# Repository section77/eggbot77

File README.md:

# eggbot77

Section77-Variante des EggBots mit ESP32 S2 mini

Willkommen! :)

Bitte prüfe zuallererst, ob Du alle Komponenten hast, die Du zum Bau Deines EggBot77 brauchst!
* [Materialliste Mechanik](./mechanics/BOM.md)
* [Materialliste Elektronik](./electronics/BOM.md)

Alles da? Super! Dann kann's ja losgehen:
* [Aufbauanleitung Mechanik](./mechanics/assembly/README.md)
* [Aufbauanleitung Elektronik](./electronics/assembly/README.md)
* [Installationsanleitung Firmware](./firmware/README.md)
* [Installationsanleitung Inkscape Plugin](./inkscape_1.x_extension/README.md)

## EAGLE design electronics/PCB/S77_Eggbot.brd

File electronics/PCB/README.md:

Design rule file jlcpcb-2layers.dru from https://github.com/oxullo/jlcpcb-eagle

CAM File for Eagle 7.7 from
https://raw.githubusercontent.com/JLCPCBofficial/jlcpcb-eagle/master/cam/jlcpcb_2_layer_v72.cam

linked from https://jlcpcb.com/help/article/9-How-to-Generate-Gerber-and-Drill-Files-in-Autodesk-Eagle

Notes when ordering at jlcpcb. From above help page:

  "Just to be safe, you can write a special instruction in the remark area in our
  ordering system when you place the order, write like:
  "Please note: there are 3 plated slotted holes in this design".
  Our CAM engineer will sort them out from the "context"
  (like the annular ring and solder mask opening) when processing the files."

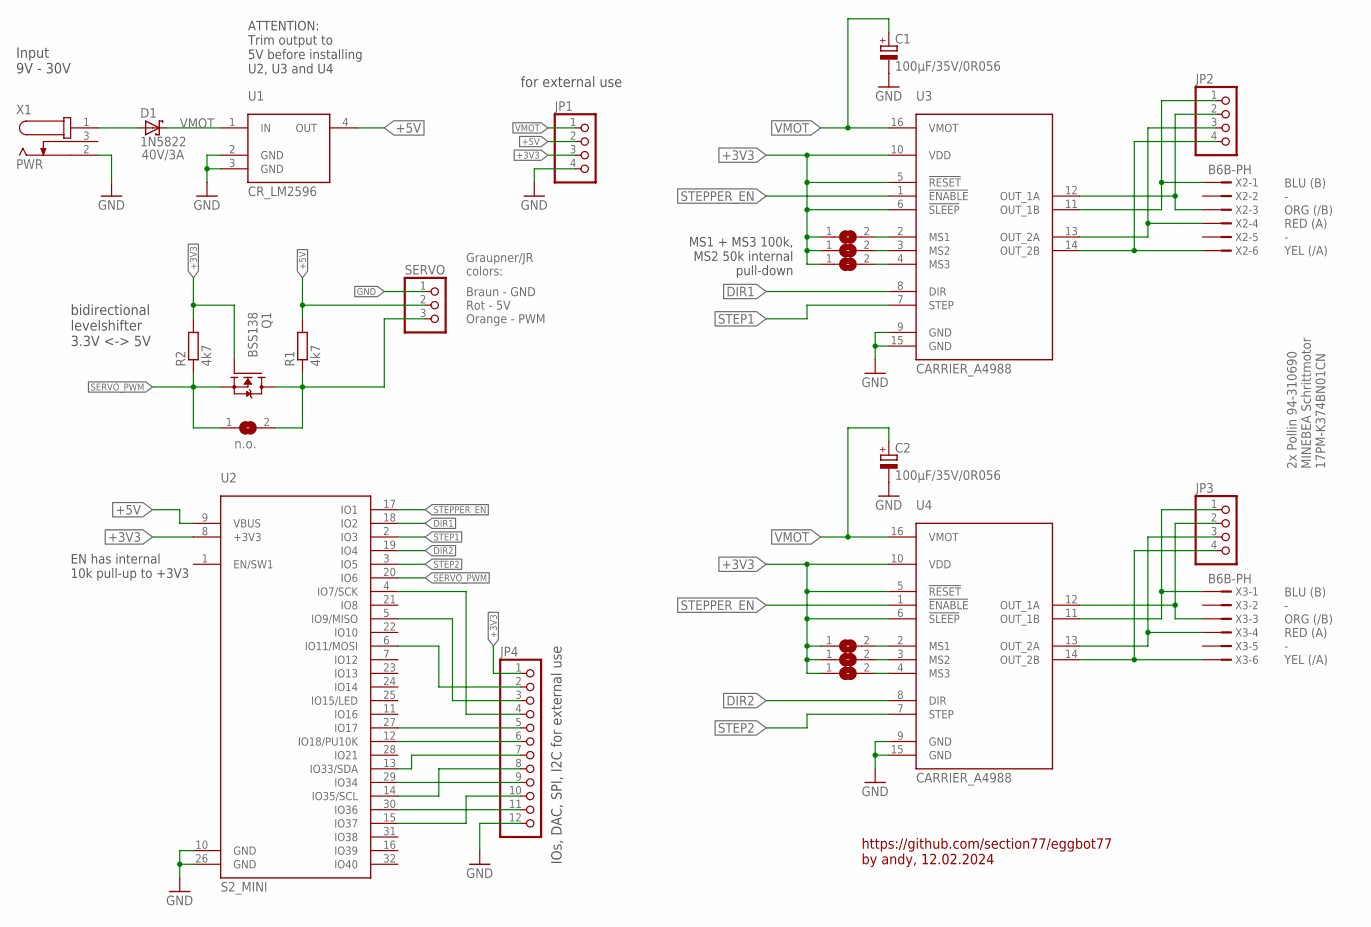
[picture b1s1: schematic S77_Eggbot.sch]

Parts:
C1, C2: 100µF/35V/0R056; E3,5-8; MPN EEUFR1V101
D1: 1N5822; DO201T15
JP1, JP2, JP3: PINHD-1X4; 1X04
JP4: PINHD-1X12; 1X12
Q1: BSS138; SOT23
R1, R2: 4k7; R1206
SERVO: PINHD-1X3; 1X03
SJ1, SJ2, SJ3, SJ4, SJ5, SJ6: SJ
SJ7: n.o.; SJ
U1: CR_LM2596
U2: S2_MINI
U3, U4: CARRIER_A4988
X1: PWR; POLLIN_JACK_A
X2, X3: B6B-PH

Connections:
+3V3: JP1.3, JP4.1, Q1.1 (G), R2.2, SJ1.1, SJ2.1, SJ3.1, SJ4.1, SJ5.1, SJ6.1, U2.8 (+3V3), U3.5 (!RESET), U3.6 (!SLEEP), U3.10 (VDD), U4.5 (!RESET), U4.6 (!SLEEP), U4.10 (VDD)
+5V: JP1.2, R1.2, SERVO.2, U1.4 (OUT), U2.9 (VBUS)
DIR1: U2.18 (IO2), U3.8 (DIR)
DIR2: U2.19 (IO4), U4.8 (DIR)
GND: C1.-, C2.-, JP1.4, JP4.12, SERVO.1, U1.2 (GND), U1.3 (GND), U2.10 (GND), U2.26 (GND), U3.9 (GND), U3.15 (GND), U4.9 (GND), U4.15 (GND), X1.2
unnamed: Q1.3 (D), R1.1, SERVO.3, SJ7.2
unnamed: JP2.1, U3.11 (OUT_1B), X2.1
unnamed: D1.A, X1.1
unnamed: JP2.2, U3.12 (OUT_1A), X2.3
unnamed: JP2.3, U3.13 (OUT_2A), X2.4
unnamed: JP2.4, U3.14 (OUT_2B), X2.6
unnamed: JP3.1, U4.11 (OUT_1B), X3.1
unnamed: JP3.2, U4.12 (OUT_1A), X3.3
unnamed: JP3.3, U4.13 (OUT_2A), X3.4
unnamed: JP3.4, U4.14 (OUT_2B), X3.6
unnamed: SJ1.2, U3.2 (MS1)
unnamed: SJ2.2, U3.3 (MS2)
unnamed: SJ3.2, U3.4 (MS3)
unnamed: SJ4.2, U4.2 (MS1)
unnamed: SJ5.2, U4.3 (MS2)
unnamed: SJ6.2, U4.4 (MS3)
unnamed: JP4.4, U2.4 (IO7/SCK)
unnamed: JP4.3, U2.5 (IO9/MISO)
unnamed: JP4.2, U2.6 (IO11/MOSI)
unnamed: JP4.5, U2.27 (IO17)
unnamed: JP4.6, U2.12 (IO18/PU10K)
unnamed: JP4.7, U2.13 (IO33/SDA)
unnamed: JP4.9, U2.29 (IO34)
unnamed: JP4.8, U2.14 (IO35/SCL)
unnamed: JP4.11, U2.30 (IO36)
unnamed: JP4.10, U2.15 (IO37)
SERVO_PWM: Q1.2 (S), R2.1, SJ7.1, U2.20 (IO6)
STEP1: U2.2 (IO3), U3.7 (STEP)
STEP2: U2.3 (IO5), U4.7 (STEP)
STEPPER_EN: U2.17 (IO1), U3.1 (!ENABLE), U4.1 (!ENABLE)
VMOT: C1.+, C2.+, D1.C, JP1.1, U1.1 (IN), U3.16 (VMOT), U4.16 (VMOT)

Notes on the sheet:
ATTENTION: Trim output to 5V before installing U2, U3 and U4
Input 9V - 30V
40V/3A
2x Pollin 94-310690 MINEBEA Schrittmotor 17PM-K374BN01CN
BLU (B) - ORG (/B) RED (A) - YEL (/A)
Braun - GND Rot - 5V Orange - PWM
MS1 + MS3 100k, MS2 50k internal pull-down
for external use
IOs, DAC, SPI, I2C for external use
EN has internal 10k pull-up to +3V3
https://github.com/section77/eggbot77 by andy, 12.02.2024
Graupner/JR colors:
bidirectional levelshifter 3.3V <-> 5V

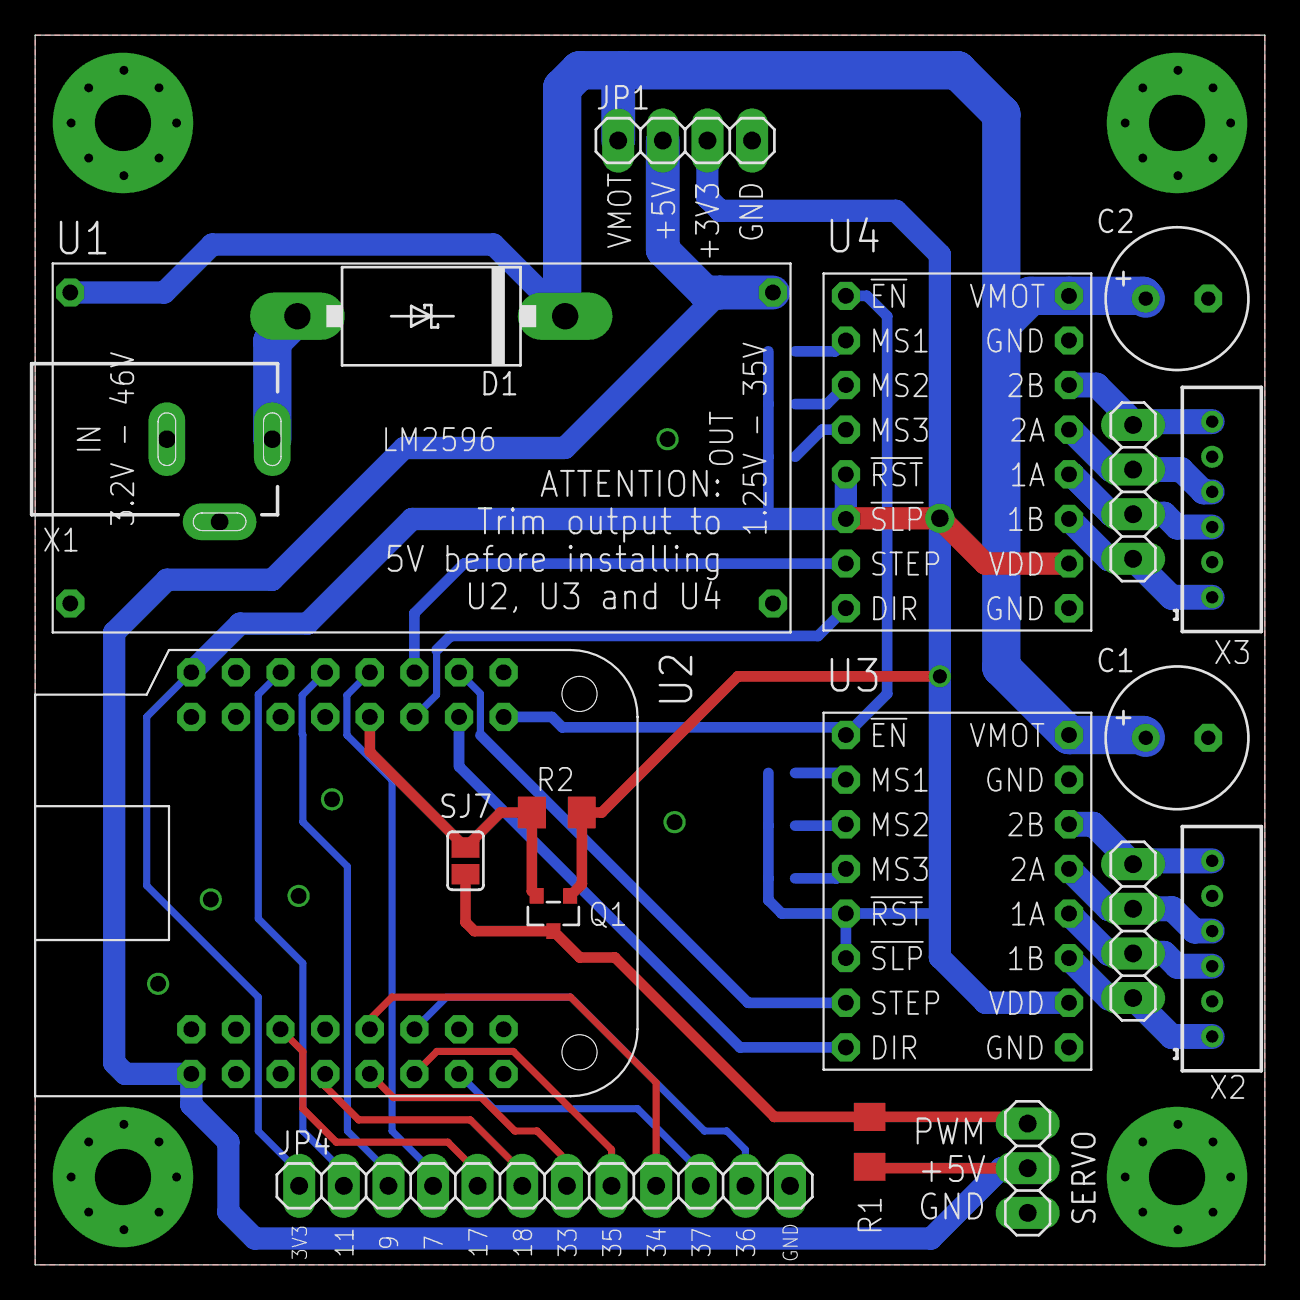
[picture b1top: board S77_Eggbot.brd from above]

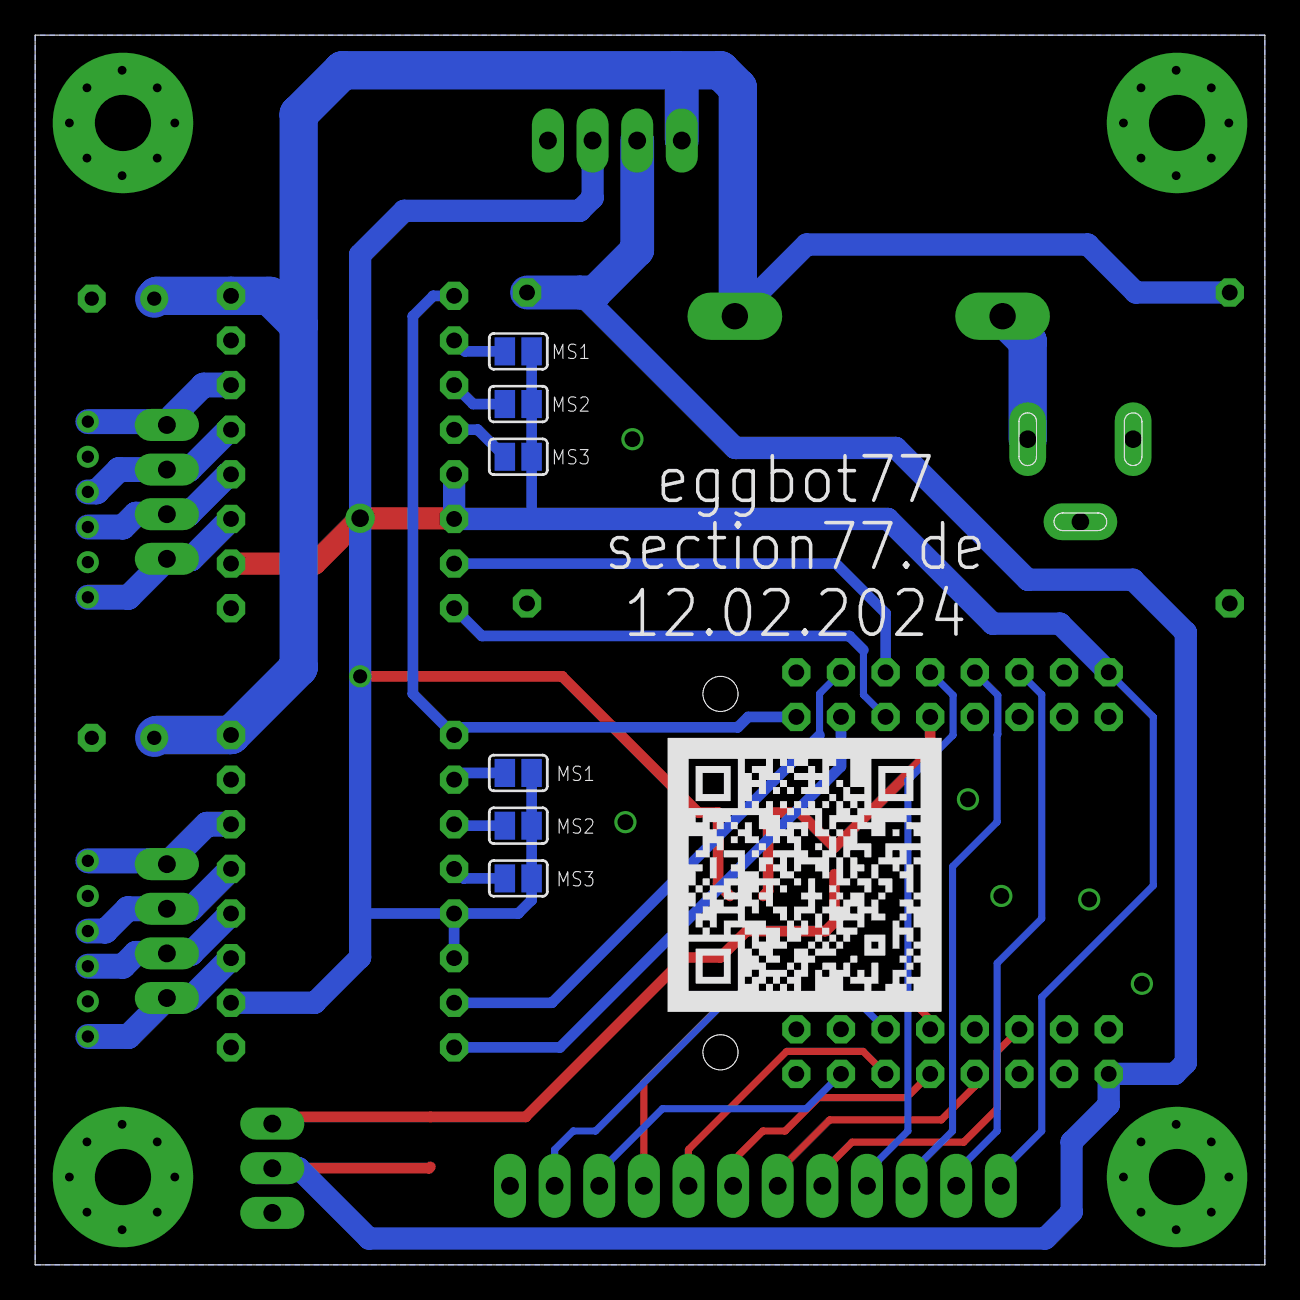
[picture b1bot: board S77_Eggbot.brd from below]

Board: 2 copper layers, 70.0 x 70.0 mm, 25 parts (6 on the bottom side), 36 nets.

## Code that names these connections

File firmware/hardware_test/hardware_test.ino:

/*
 * Simple hardware test for the EggBot77 version 25.01.2024
 * Servo sweeps between 850µs and 2150 and both steppers
 * run in velocity mode with step frequency between 440Hz and 7040 Hz.
 *
 * Attention: The stepper motors make several fast revolutions.
 * The program should therefore only be executed as long as the servo
 * and stepper motors have not yet been installed.
 */

#include <driver/ledc.h>

#define STEPPER_EN 1  // for both steppers
#define DIR1 2
#define STEP1 3
#define DIR2 4
#define STEP2 5
#define LED_BUILTIN 15  // the blue onboard LED

#define SERVO_PWM 6

// ESP32 LED Controller (we use them here for generating servo PWM and stepper frequencies)
#define SERVO_LEDC_CH 1
#define STEP1_LEDC_CH 2
#define STEP2_LEDC_CH 3

#define FREQ_HIGH 7040
#define FREQ_LOW 220

hw_timer_t *Timer0_Cfg = NULL;

void set_freq(uint8_t ch, int16_t freq) {
  ledcSetup(ch, freq, 10);  // 14bit
  ledcWrite(ch, (1 << 9));  // 50% duty cycle
}

// 200Hz/5ms task
void IRAM_ATTR Timer0_ISR() {
  static uint16_t cnt = 0;

  // toggle blue onboard LED every 500ms
  if (cnt % 100 == 0)
    digitalWrite(LED_BUILTIN, !digitalRead(LED_BUILTIN));

  // sweep servo
  {
    const int16_t min_width = 850;   // [µs]
    const int16_t max_width = 2150;  // [µs]
    static int8_t pwm_inc = 1;       // ramp slope, µs width per 10ms

    static int16_t pwm_width = min_width;
    pwm_width += pwm_inc;
    if (pwm_width > max_width) {
      pwm_width = max_width;
      pwm_inc *= -1;
    } else if (pwm_width < min_width) {
      pwm_width = min_width;
      pwm_inc *= -1;
    }
    int16_t pwm_val = pwm_width * 4096 / 20000;
    ledcWrite(SERVO_LEDC_CH, pwm_val);
  }

  // both servos in velocity mode
  // change frequency every second
  if (cnt % 200 == 0) {
    static int16_t freq = FREQ_LOW;
    static int8_t freq_dir = 1;  // 0 = down, 1 = up

    if (freq_dir == 1) {
      freq = freq * 2;
      if (freq >= FREQ_HIGH) {
        freq_dir = 0;
      }
    } else if (freq_dir == 0) {
      freq = freq / 2;
      if (freq <= FREQ_LOW) {
        freq = FREQ_LOW;
        freq_dir = 1;
        digitalWrite(DIR1, !digitalRead(DIR1));
        digitalWrite(DIR2, !digitalRead(DIR2));
      }
    }
    Serial.printf("Setting stepper frequency to %i Hz...\n", freq);
    set_freq(STEP1_LEDC_CH, freq);
    set_freq(STEP2_LEDC_CH, freq);
  }
  cnt++;
}

void setup() {
  Serial.begin(9600);
  Serial.setDebugOutput(true);

  // delay 2000ms so the Serial Monitor can reconnect to USB CDC after flashing
  delay(2000);
  Serial.println("This is " __FILE__ ", compiled at " __DATE__ ", " __TIME__);

  // enable both steppers permanently (active low)
  pinMode(STEPPER_EN, OUTPUT);
  digitalWrite(STEPPER_EN, LOW);

  pinMode(DIR1, OUTPUT);
  digitalWrite(DIR1, LOW);
  pinMode(DIR2, OUTPUT);
  digitalWrite(DIR2, LOW);

  pinMode(LED_BUILTIN, OUTPUT);

  // attach Servo PWM pin to channel 2
  ledcAttachPin(SERVO_PWM, SERVO_LEDC_CH);
  ledcSetup(SERVO_LEDC_CH, 50, 12);

  // attach both STEP pins for the steppers
  ledcAttachPin(STEP1, STEP1_LEDC_CH);
  ledcAttachPin(STEP2, STEP2_LEDC_CH);
  set_freq(STEP1_LEDC_CH, FREQ_LOW);
  set_freq(STEP2_LEDC_CH, FREQ_LOW);

  // configure 5ms timer
  Timer0_Cfg = timerBegin(0, 80, true);
  timerAttachInterrupt(Timer0_Cfg, &Timer0_ISR, true);
  timerAlarmWrite(Timer0_Cfg, 5000, true);  // 80MHz/80/5000 -> 5ms task

  // enable it
  timerAlarmEnable(Timer0_Cfg);
  Serial.println("leaving setup()...");
}

void loop() {
  // nothing here, all work is done in timer interrupt
}

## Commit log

2024-01-17 Add Eagle schematic and library
2024-01-17 Add .gitkeep as dummy for new folders
2024-01-20 add most stl files
2024-01-21 add remaining print files and update readme
2024-01-24 Add DRU, CAM and add ordering notes for jlcpcb
2024-01-24 WIP: fix board dimension and place components
2024-01-24 first version of schematic and layout
2024-01-25 PCB: fix smaller details, update docs
2024-01-25 Add QR Code to board layout, export gerber files
2024-01-25 Add section77.de to board, increase clearance to 8mil
2024-02-05 increase diameter for spring bolt
2024-02-05 add hint for shipping method
2024-02-05 Fix: swap Pin 1 and 2 on barrel jack X1
2024-02-08 clone from gesinas fork, see README.md
2024-02-08 extract firmware from https://github.com/Andy1978/EggDuino
2024-02-09 Move firmware in separate directory, arduino-ide complains if not
2024-02-09 firmware: Add hardware test and README to describe directory
2024-02-09 docs: Add esp32_technical_reference_manual_en
2024-02-09 Update CAM file (output path to deperate directory)
2024-02-09 PCB: update date
2024-02-09 firmware: Use ESP32 LED Controller PWM for pen servo up/down
2024-02-09 firmware doc: Image of board select in arduino IDE
2024-02-09 Playground angelegt
2024-02-09 inkscape extension, add new PID and name after update to arduino IDE 2.3.0
2024-02-09 playground: simple script to test steppers
2024-02-10 Firmware: fix minimal STEP width (1µs for A4988) on ESP32 S2 mini
2024-02-10 test_steppers.m: extend to autodetect port and run more tests
2024-02-12 Add description to patch Inkscape AppImage
2024-02-12 README.md: fix copy & paste error
2024-02-12 Fix footprint for pollin 5.5/2.1mm and 5.5/2.5mm jacks
2024-02-12 EBBHardware.cpp: use define for Servo Pin LED Controller channel
2024-02-12 PCB: added 3.3V<->5V levelshifter for servo PWM, update exports
2024-02-15 remove old variants of stl files
2024-02-15 modify spring to suit new screw type
2024-02-15 add new version of stepper holder, created by michaelf, precision adjustments by bruder-jo - thank you! :)
2024-02-15 add rotational stepper holder with holes drilled all the way - thx to bruder-jo!
2024-02-16 firmware/EggBot77: fix conditional compiling without engraver
2024-02-22 extend hardware test to drive both steppers and pen servo
2024-03-15 BOM.md: Reichelt Bauteile für 5V PWM hinzugefügt
2024-03-15 third_party_docs: Auch den Schrittmotor hinzugefügt
2024-03-15 assembly: add images for assembly instruction
2024-03-15 README.de.md: erste Version der Aufbauanleitung
2024-03-15 EggBot77 firmware: minor cleanup
2024-03-15 README.de.md: 2 zusätzliche Bilder, besser erklärt
2024-03-15 Readme erweitert, ins englische übersetzt
2024-03-16 Fix links in assemnly instructions
2024-03-16 Update READMEs
2024-03-17 apply bruder-jo's fix for spring - thx\!
2024-03-17 add Pen Knob by Smuk3D (https://www.thingiverse.com/thing:1450115/files)
2024-03-17 refine inner wall
2024-03-21 improvements for better printability by bruder-jo - thx!!!
2024-03-23 improve eierhalter lagerseite for better printability - thx to bruder-jo!
2024-03-24 fix a typo
2024-03-24 add hint for to get the steppers connected correctly at first try
2024-03-24 reorganize dir structure, add more print files
2024-03-24 add link to OpenSCAD files for eierhalter
2024-03-24 add more README files
2024-03-24 add pics for assembly instructions
2024-03-24 add assembly instructions for mechanics
2024-03-24 add default README
2024-03-24 add multilang support for instructions
2024-03-24 add direct link to component pic
2024-03-24 add more pics and update README
2024-03-24 fix syntax
2024-03-25 add more pics, update README
2024-03-25 remove stale files
2024-03-25 fix file names, add pics
2024-03-25 fix file names
2024-03-25 add german version, refine english one
2024-03-25 refine english readme
2024-03-25 refine formatting
2024-03-26 fix links, add pic
2024-03-26 add german version of installation instructions for plugin
2024-03-26 add language selectors
2024-03-26 inkscape plugin: disable steppers after plotting
2024-03-26 inkscape plugin: change link to section77 repo
2024-03-26 update links in README
2024-03-26 add BOMs for mechanics
2024-03-26 translate heading
2024-03-26 add group photos of the whole class
2024-03-26 fix path, fix order of components
2024-03-26 add credits
2024-03-27 fix filenames
2024-03-27 fix typo
2024-03-27 add spacer
2024-03-27 replace pics by stls
2024-03-27 update docs
2024-03-27 remove temp item
2024-03-27 update BOM
2024-03-29 replace link
2024-04-01 fix: wrong installation path for Inkscape plugin
    I noticed a wrong path during installation of the plugin. This commit shows the correct path for a successful windows installation.
2024-04-02 replicate path correction (see PR #15) to english, minor wording changes
2024-04-14 add more specific details for BOMs
2024-04-22 fix issue Anleitung Stangen falsch: oben unten vertauscht #8
2025-02-22 decrease width of toolmount to fix #9
2025-03-02 fix sequence for assembly: mechanics first, electronics next
2025-03-03 add required tools
2025-03-03 add Eierhalter Lagerseite to steps
2025-03-20 refine print files
2025-04-18 first part of cleanup
2025-04-18 more fixes
2025-04-18 add new pics
2025-04-18 even more
2025-04-18 fix file name
2025-04-18 even more fixes
2025-04-18 fix format
2025-04-18 Dev 2025 eh22 (#17)
    * decrease width of toolmount to fix #9
    * fix sequence for assembly: mechanics first, electronics next
    * add required tools
    * add Eierhalter Lagerseite to steps
    * refine print files
    * first part of cleanup
2025-04-19 fix tool size
2025-04-20 fix for arduino-esp32 v2->v3 migration,
    see https://github.com/espressif/arduino-esp32/blob/master/docs/en/migration_guides/2.x_to_3.0.rst#ledc
    and https://github.com/section77/eggbot77/issues/19
2025-04-22 fix pin (2 -> 6)
2025-04-22 Arduino esp32 v2 to v3 (#27)
    * fix for arduino-esp32 v2->v3 migration,
    see https://github.com/espressif/arduino-esp32/blob/master/docs/en/migration_guides/2.x_to_3.0.rst#ledc
    and https://github.com/section77/eggbot77/issues/19
    * fix pin (2 -> 6)
    ---------
    Authored-by: Andreas Weber <andy@josoansi.de>
2026-03-30 duplicate all changes to english version
2026-03-30 add the big tpu pads
2026-03-30 update filenames
2026-03-31 fix file names, fix text
2026-04-03 Dev 2025 eh22 -> main (#28)
    * decrease width of toolmount to fix #9
    * fix sequence for assembly: mechanics first, electronics next
    * add required tools
    * add Eierhalter Lagerseite to steps
    * refine print files
    * first part of cleanup
